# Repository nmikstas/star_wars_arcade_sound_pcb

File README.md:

# star_wars_arcade_sound_pcb
Reproduction of the Star Wars arcade sound PCB. The PCB is complete but not yet verified.

# Folder Structure
* BOM - Bill of materials for the sound PCB
* Gerbers - The gerber files for the sound PCB
* images - The images used for the sound PCB
* pcb - The Kicad design files for the sound PCB

# PCB Specifications
* Layers: 2
* Dimensions: 293mm X 227mm
* Different PCB Design: 1
* PCB Thickness: 1.6mm
* Surface Finish: HASL
* Castellated Holes: No
* Copper Weight: 1oz.

# The Complete Star Wars Arcade PCB Repository Collection
* Main PCB: https://github.com/nmikstas/star_wars_arcade_main_pcb
* AVG PCB: https://github.com/nmikstas/star_wars_arcade_avg_pcb
* Sound PCB: https://github.com/nmikstas/star_wars_arcade_sound_pcb
* EMI PCB: https://github.com/nmikstas/star_wars_arcade_emi_pcb
* Interconnect PCB: 
* AVG Chip: https://github.com/nmikstas/atari-avg-replacements
* Varistor Replacement: https://github.com/nmikstas/atari_voltage_dependent_resistor
* Mathbox ROM Replacement:
* State Machine Adapter PCB:

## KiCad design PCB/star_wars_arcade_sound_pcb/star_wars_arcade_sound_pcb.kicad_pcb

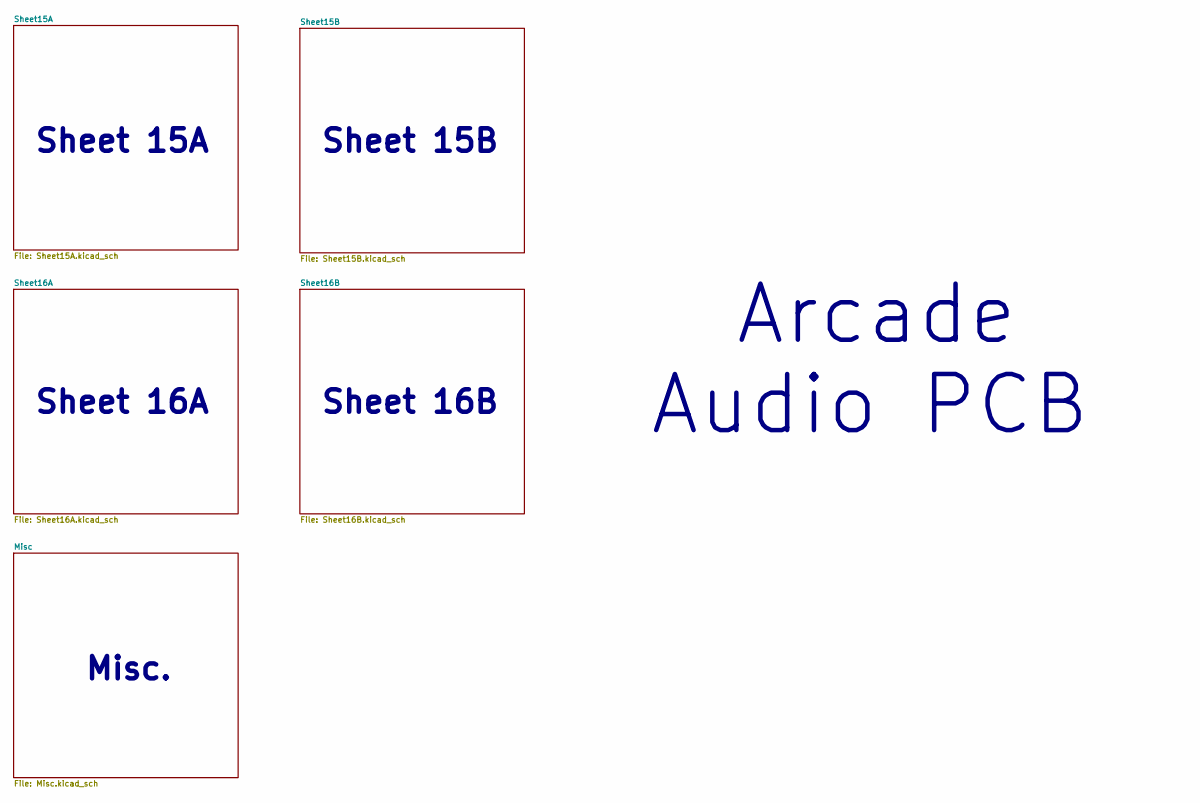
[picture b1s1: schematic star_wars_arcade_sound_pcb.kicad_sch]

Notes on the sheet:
Sheet 15A
Sheet 16A
Sheet 15B
Arcade Audio PCB
Sheet 16B
Misc.

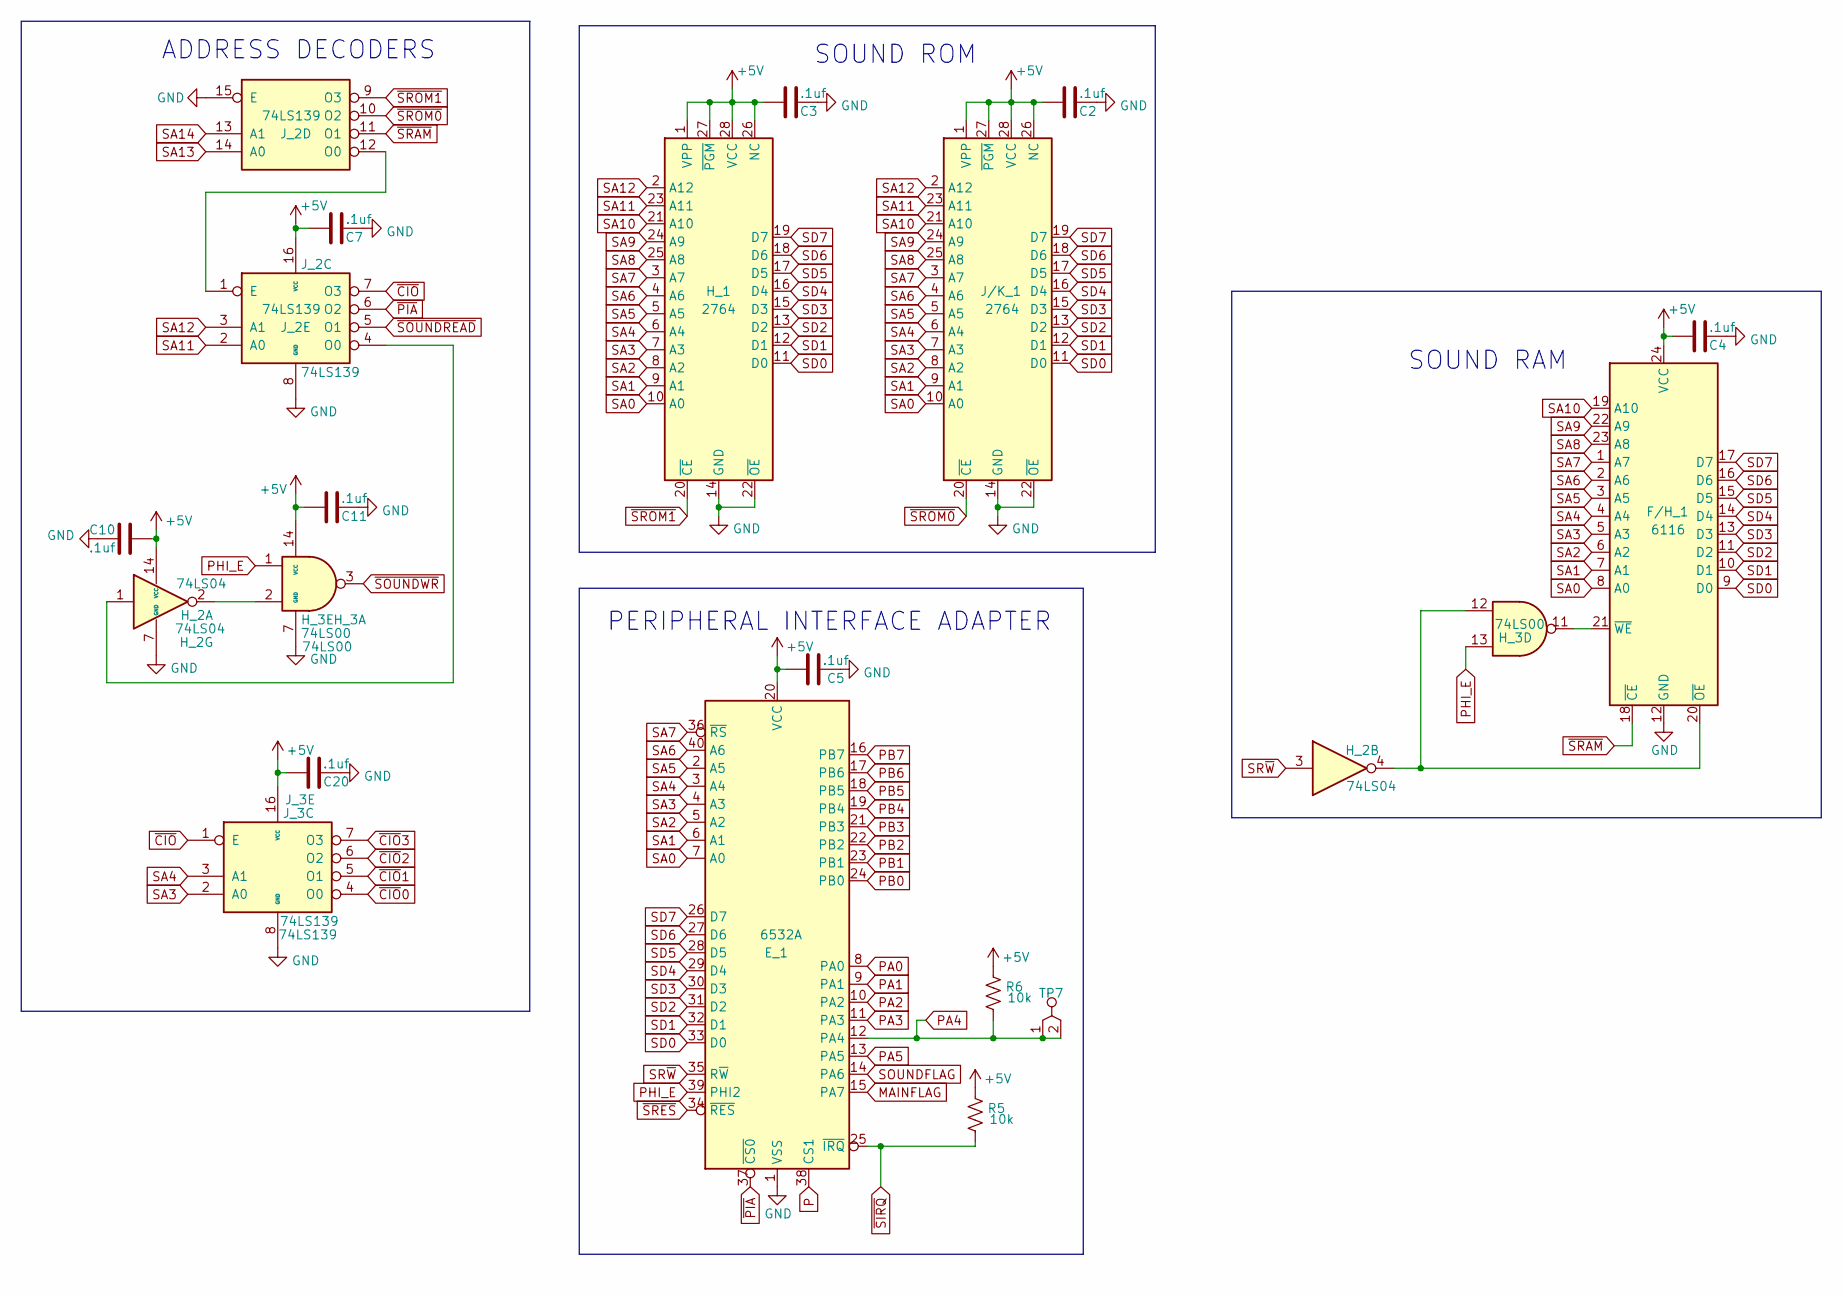
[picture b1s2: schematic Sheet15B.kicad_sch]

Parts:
C2, C3, C4, C5, C7, C10, C11, C20: .1uf; GenericComp
E_1: 6532A; DDIP40
F/H_1: 6116; DDIP24
H_1: 2764; DIP28
H_2: 74LS04; DIP14
H_3: 74LS00; DIP14
J/K_1: 2764; DIP28
J_2, J_3: 74LS139; DIP16
R5, R6: 10k; GenericComp
TP7: tp_2_pin; TEST_POINT

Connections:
+5V: C2.1, C3.1, C4.1, C5.1, C7.1, C10.1, C11.1, C20.1, E_1.20 (VCC), F/H_1.24 (VCC), H_1.1 (VPP), H_1.26 (NC), H_1.27 (~PGM), H_1.28 (VCC), H_2.14 (VCC), H_3.14 (VCC), J/K_1.1 (VPP), J/K_1.26 (NC), J/K_1.27 (~PGM), J/K_1.28 (VCC), J_2.16 (VCC), J_3.16 (VCC), R5.1, R6.1; also elsewhere on the board
GND: C2.2, C3.2, C4.2, C5.2, C7.2, C10.2, C11.2, C20.2, E_1.1 (VSS), F/H_1.12 (GND), H_1.14 (GND), H_1.22 (~OE), H_2.7 (GND), H_3.7 (GND), J/K_1.14 (GND), J/K_1.22 (~OE), J_2.8 (GND), J_2.15 (E), J_3.8 (GND); also elsewhere on the board
MAINFLAG: E_1.15 (PA7); also elsewhere on the board
unnamed: F/H_1.20 (~OE), H_2.4, H_3.12
unnamed: F/H_1.21 (~WE), H_3.11
unnamed: H_2.1, J_2.4 (O0)
unnamed: H_2.2, H_3.2
unnamed: J_2.1 (E), J_2.12 (O0)
P: E_1.38 (CS1); also elsewhere on the board
PA0: E_1.8 (PA0); also elsewhere on the board
PA1: E_1.9 (PA1); also elsewhere on the board
PA2: E_1.10 (PA2); also elsewhere on the board
PA3: E_1.11 (PA3); also elsewhere on the board
PA4: E_1.12 (PA4), R6.2, TP7.1, TP7.2
PA5: E_1.13 (PA5); also elsewhere on the board
PB0: E_1.24 (PB0); also elsewhere on the board
PB1: E_1.23 (PB1); also elsewhere on the board
PB2: E_1.22 (PB2); also elsewhere on the board
PB3: E_1.21 (PB3); also elsewhere on the board
PB4: E_1.19 (PB4); also elsewhere on the board
PB5: E_1.18 (PB5); also elsewhere on the board
PB6: E_1.17 (PB6); also elsewhere on the board
PB7: E_1.16 (PB7); also elsewhere on the board
PHI_E: E_1.39 (PHI2), H_3.1, H_3.13; also elsewhere on the board
SA0: E_1.7 (A0), F/H_1.8 (A0), H_1.10 (A0), J/K_1.10 (A0); also elsewhere on the board
SA1: E_1.6 (A1), F/H_1.7 (A1), H_1.9 (A1), J/K_1.9 (A1); also elsewhere on the board
SA2: E_1.5 (A2), F/H_1.6 (A2), H_1.8 (A2), J/K_1.8 (A2); also elsewhere on the board
SA3: E_1.4 (A3), F/H_1.5 (A3), H_1.7 (A3), J/K_1.7 (A3), J_3.2 (A0); also elsewhere on the board
SA4: E_1.3 (A4), F/H_1.4 (A4), H_1.6 (A4), J/K_1.6 (A4), J_3.3 (A1); also elsewhere on the board
SA5: E_1.2 (A5), F/H_1.3 (A5), H_1.5 (A5), J/K_1.5 (A5); also elsewhere on the board
SA6: E_1.40 (A6), F/H_1.2 (A6), H_1.4 (A6), J/K_1.4 (A6); also elsewhere on the board
SA7: E_1.36 (~RS), F/H_1.1 (A7), H_1.3 (A7), J/K_1.3 (A7); also elsewhere on the board
SA8: F/H_1.23 (A8), H_1.25 (A8), J/K_1.25 (A8); also elsewhere on the board
SA9: F/H_1.22 (A9), H_1.24 (A9), J/K_1.24 (A9); also elsewhere on the board
SA10: F/H_1.19 (A10), H_1.21 (A10), J/K_1.21 (A10); also elsewhere on the board
SA11: H_1.23 (A11), J/K_1.23 (A11), J_2.2 (A0); also elsewhere on the board
SA12: H_1.2 (A12), J/K_1.2 (A12), J_2.3 (A1); also elsewhere on the board
SA13: J_2.14 (A0); also elsewhere on the board
SA14: J_2.13 (A1); also elsewhere on the board
SD0: E_1.33 (D0), F/H_1.9 (D0), H_1.11 (D0), J/K_1.11 (D0); also elsewhere on the board
SD1: E_1.32 (D1), F/H_1.10 (D1), H_1.12 (D1), J/K_1.12 (D1); also elsewhere on the board
SD2: E_1.31 (D2), F/H_1.11 (D2), H_1.13 (D2), J/K_1.13 (D2); also elsewhere on the board
SD3: E_1.30 (D3), F/H_1.13 (D3), H_1.15 (D3), J/K_1.15 (D3); also elsewhere on the board
SD4: E_1.29 (D4), F/H_1.14 (D4), H_1.16 (D4), J/K_1.16 (D4); also elsewhere on the board
SD5: E_1.28 (D5), F/H_1.15 (D5), H_1.17 (D5), J/K_1.17 (D5); also elsewhere on the board
SD6: E_1.27 (D6), F/H_1.16 (D6), H_1.18 (D6), J/K_1.18 (D6); also elsewhere on the board
SD7: E_1.26 (D7), F/H_1.17 (D7), H_1.19 (D7), J/K_1.19 (D7); also elsewhere on the board
SOUNDFLAG: E_1.14 (PA6); also elsewhere on the board
SR~W: E_1.35 (R~W), H_2.3; also elsewhere on the board
~CIO: J_2.7 (O3), J_3.1 (E)
~CIO0: J_3.4 (O0); also elsewhere on the board
~CIO1: J_3.5 (O1); also elsewhere on the board
~CIO2: J_3.6 (O2); also elsewhere on the board
~CIO3: J_3.7 (O3); also elsewhere on the board
~PIA: E_1.37 (~CS0), J_2.6 (O2)
~SIRQ: E_1.25 (~IRQ), R5.2; also elsewhere on the board
~SOUNDREAD: J_2.5 (O1); also elsewhere on the board
~SOUNDWR: H_3.3; also elsewhere on the board
~SRAM: F/H_1.18 (~CE), J_2.11 (O1)
~SRES: E_1.34 (~RES); also elsewhere on the board
~SROM0: J/K_1.20 (~CE), J_2.10 (O2)
~SROM1: H_1.20 (~CE), J_2.9 (O3)

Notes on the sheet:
PERIPHERAL INTERFACE ADAPTER
ADDRESS DECODERS
SOUND RAM
SOUND ROM

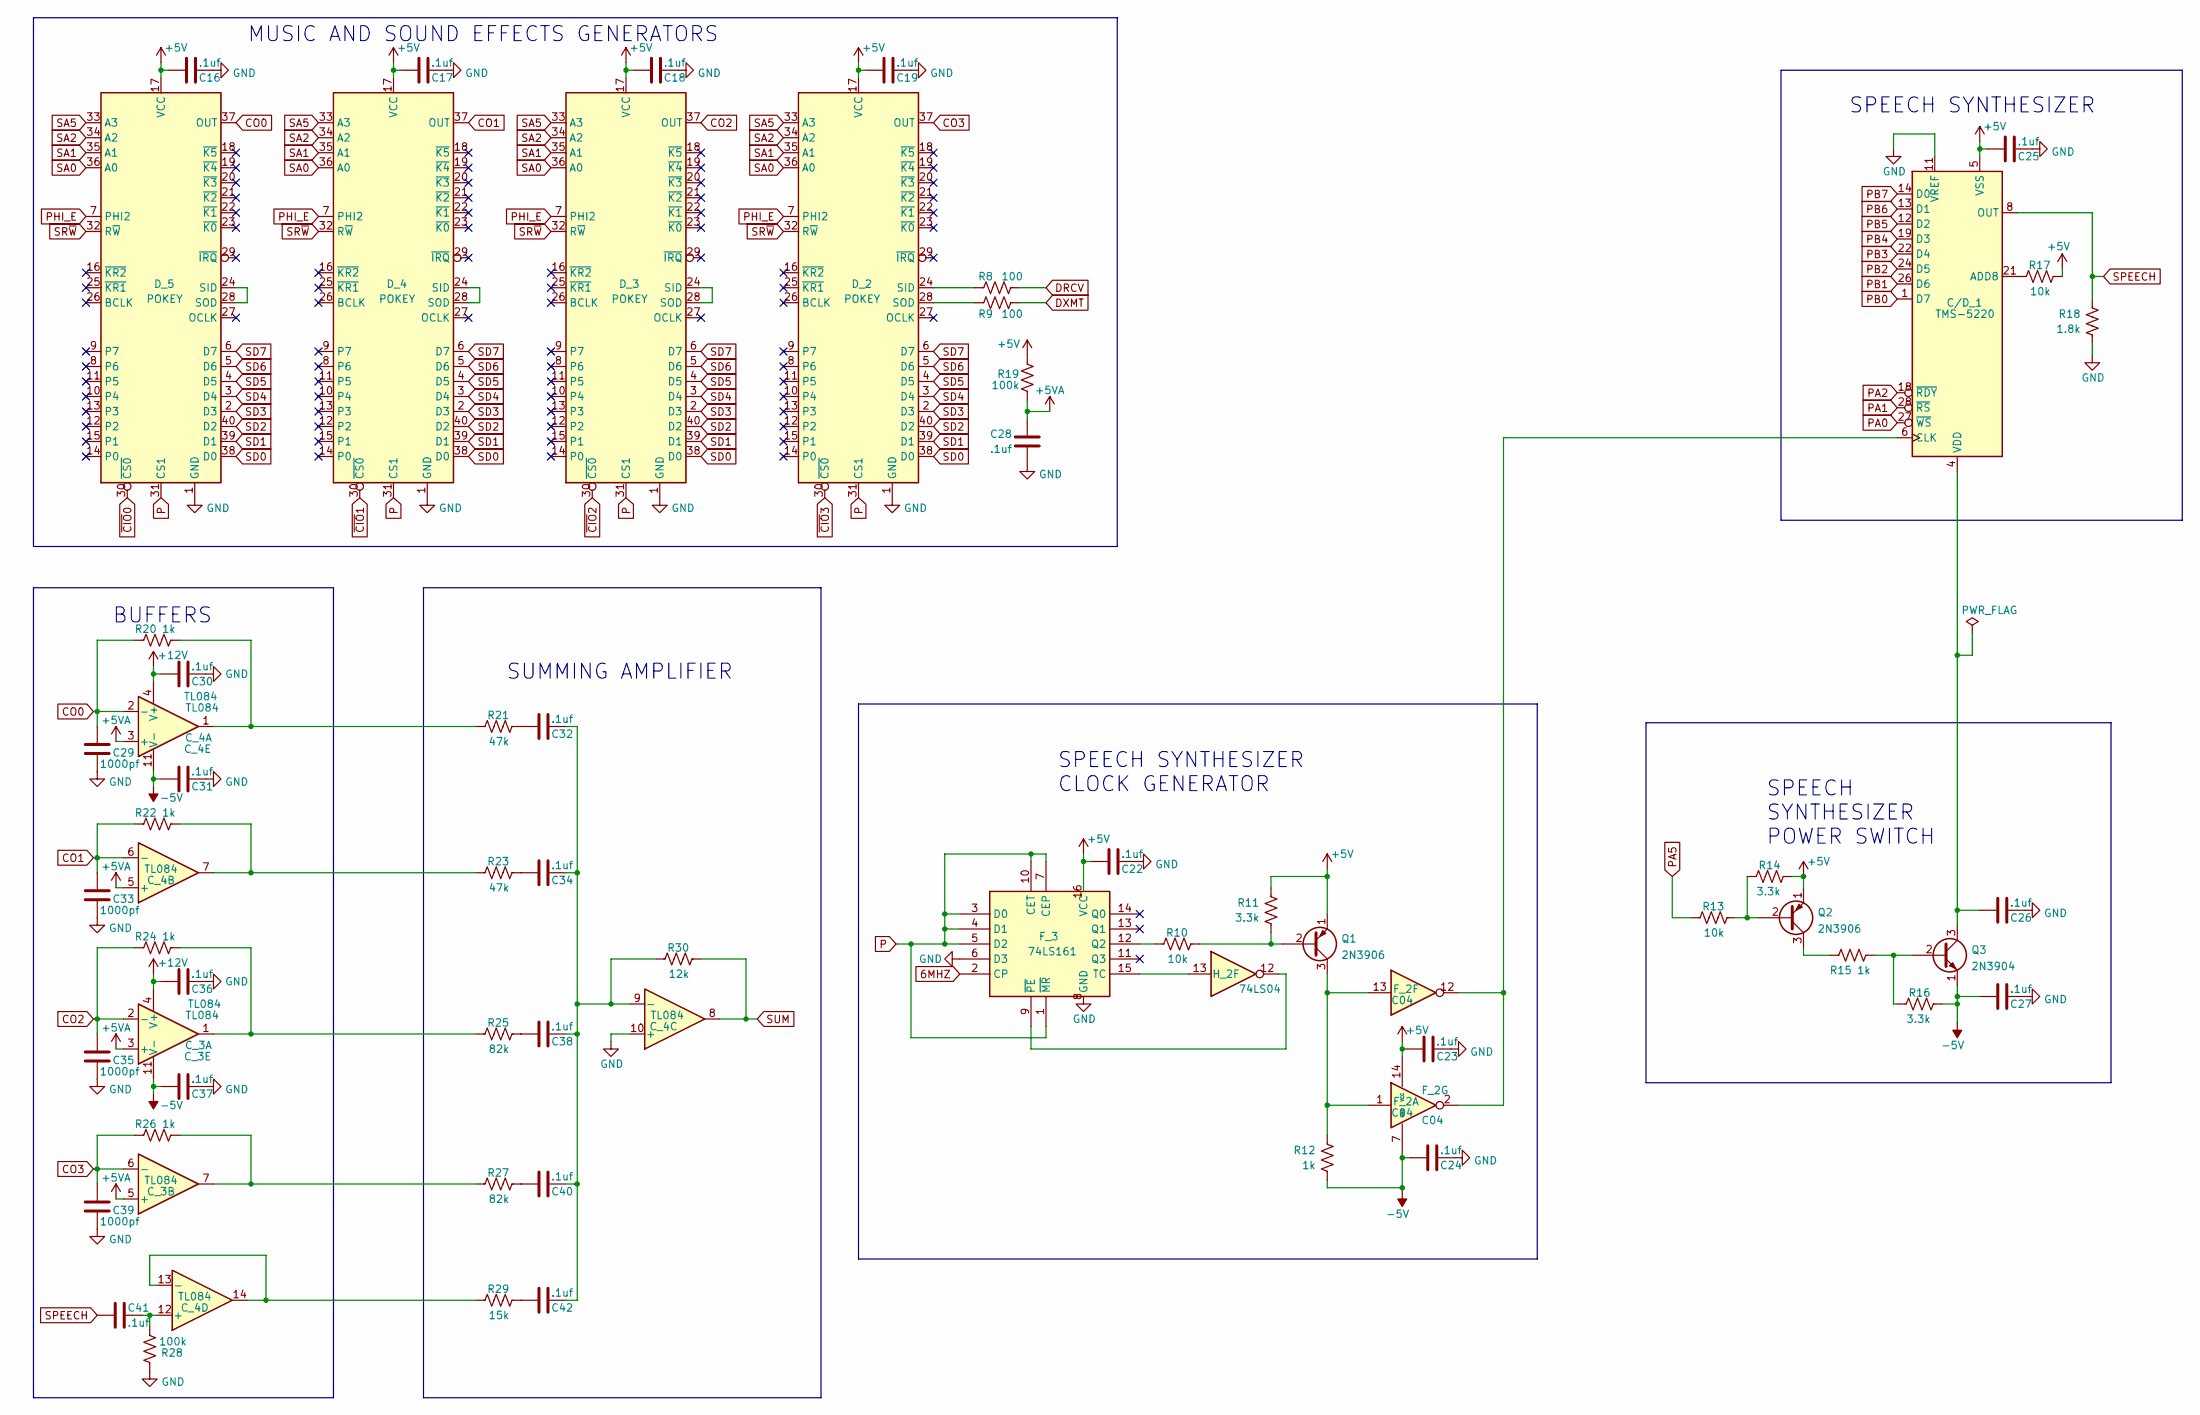
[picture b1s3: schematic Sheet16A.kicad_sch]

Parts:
C16, C17, C18, C19, C22, C23, C24, C25, C26, C27, C28, C30, C31, C32, C34, C36, C37, C38, C40, C41, C42: .1uf; GenericComp
C29, C33, C35, C39: 1000pf; GenericComp
C/D_1: TMS-5220; DIP28
C_3, C_4: TL084; DIP14
D_2, D_3, D_4, D_5: POKEY; DDIP40
F_2: C04; DIP14
F_3: 74LS161; DIP16
H_2: 74LS04; DIP14
Q1, Q2: 2N3906; GenericTrans
Q3: 2N3904; GenericTrans
R8, R9: 100; GenericComp
R10, R13, R17: 10k; GenericComp
R11, R14, R16: 3.3k; GenericComp
R12, R15, R20, R22, R24, R26: 1k; GenericComp
R18: 1.8k; GenericComp
R19, R28: 100k; GenericComp
R21, R23: 47k; GenericComp
R25, R27: 82k; GenericComp
R29: 15k; GenericComp
R30: 12k; GenericComp

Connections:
6MHZ: F_3.2 (CP); also elsewhere on the board
+5V: C16.1, C17.1, C18.1, C19.1, C22.1, C23.1, C25.1, C/D_1.5 (VSS), D_2.17 (VCC), D_3.17 (VCC), D_4.17 (VCC), D_5.17 (VCC), F_2.14 (VCC), F_3.16 (VCC), Q1.1 (E), Q2.1 (E), R11.2, R14.2, R17.2, R19.2; also elsewhere on the board
+5VA: C28.2, C_3.3 (+), C_3.5 (+), C_4.3 (+), C_4.5 (+), R19.1
+12V: C30.1, C36.1, C_3.4 (V+), C_4.4 (V+); also elsewhere on the board
-5V: C24.1, C27.1, C31.1, C37.1, C_3.11 (V-), C_4.11 (V-), F_2.7 (GND), Q3.1 (E), R12.1, R16.2; also elsewhere on the board
CO0: C29.2, C_4.2 (-), D_5.37 (OUT), R20.1
CO1: C33.2, C_4.6 (-), D_4.37 (OUT), R22.1
CO2: C35.2, C_3.2 (-), D_3.37 (OUT), R24.1
CO3: C39.2, C_3.6 (-), D_2.37 (OUT), R26.1
DRCV: R8.2; also elsewhere on the board
DXMT: R9.2; also elsewhere on the board
GND: C16.2, C17.2, C18.2, C19.2, C22.2, C23.2, C24.2, C25.2, C26.2, C27.2, C28.1, C29.1, C30.2, C31.2, C33.1, C35.1, C36.2, C37.2, C39.1, C/D_1.11 (VREF), C_4.10 (+), D_2.1 (GND), D_3.1 (GND), D_4.1 (GND), D_5.1 (GND), F_3.6 (D3), F_3.8 (GND), R18.1, R28.1; also elsewhere on the board
unnamed: C32.1, R21.2
unnamed: C32.2, C34.2, C38.2, C40.2, C42.2, C_4.9 (-), R30.1
unnamed: C34.1, R23.2
unnamed: C38.1, R25.2
unnamed: C40.1, R27.2
unnamed: C41.1, C_4.12 (+), R28.2
unnamed: C42.1, R29.2
unnamed: C26.1, C/D_1.4 (VDD), Q3.3 (C)
unnamed: C/D_1.6 (CLK), F_2.2, F_2.12
unnamed: C/D_1.21 (ADD8), R17.1
unnamed: C_3.1, R24.2, R25.1
unnamed: C_3.7, R26.2, R27.1
unnamed: C_4.1, R20.2, R21.1
unnamed: C_4.7, R22.2, R23.1
unnamed: C_4.13 (-), C_4.14, R29.1
unnamed: D_2.24 (SID), R8.1
unnamed: D_2.28 (SOD), R9.1
unnamed: D_3.24 (SID), D_3.28 (SOD)
unnamed: D_4.24 (SID), D_4.28 (SOD)
unnamed: D_5.24 (SID), D_5.28 (SOD)
unnamed: F_2.1, F_2.13, Q1.3 (C), R12.2
unnamed: F_3.9 (~PE), H_2.12
unnamed: F_3.12 (Q2), R10.1
unnamed: F_3.15 (TC), H_2.13
unnamed: Q1.2 (B), R10.2, R11.1
unnamed: Q2.2 (B), R13.2, R14.1
unnamed: Q2.3 (C), R15.1
unnamed: Q3.2 (B), R15.2, R16.1
P: D_2.31 (CS1), D_3.31 (CS1), D_4.31 (CS1), D_5.31 (CS1), F_3.1 (~MR), F_3.3 (D0), F_3.4 (D1), F_3.5 (D2), F_3.7 (CEP), F_3.10 (CET); also elsewhere on the board
PA0: C/D_1.27 (~WS); also elsewhere on the board
PA1: C/D_1.28 (~RS); also elsewhere on the board
PA2: C/D_1.18 (~RDY); also elsewhere on the board
PA5: R13.1; also elsewhere on the board
PB0: C/D_1.1 (D7); also elsewhere on the board
PB1: C/D_1.26 (D6); also elsewhere on the board
PB2: C/D_1.24 (D5); also elsewhere on the board
PB3: C/D_1.22 (D4); also elsewhere on the board
PB4: C/D_1.19 (D3); also elsewhere on the board
PB5: C/D_1.12 (D2); also elsewhere on the board
PB6: C/D_1.13 (D1); also elsewhere on the board
PB7: C/D_1.14 (D0); also elsewhere on the board
PHI_E: D_2.7 (PHI2), D_3.7 (PHI2), D_4.7 (PHI2), D_5.7 (PHI2); also elsewhere on the board
SA0: D_2.36 (A0), D_3.36 (A0), D_4.36 (A0), D_5.36 (A0); also elsewhere on the board
SA1: D_2.35 (A1), D_3.35 (A1), D_4.35 (A1), D_5.35 (A1); also elsewhere on the board
SA2: D_2.34 (A2), D_3.34 (A2), D_4.34 (A2), D_5.34 (A2); also elsewhere on the board
SA5: D_2.33 (A3), D_3.33 (A3), D_4.33 (A3), D_5.33 (A3); also elsewhere on the board
SD0: D_2.38 (D0), D_3.38 (D0), D_4.38 (D0), D_5.38 (D0); also elsewhere on the board
SD1: D_2.39 (D1), D_3.39 (D1), D_4.39 (D1), D_5.39 (D1); also elsewhere on the board
SD2: D_2.40 (D2), D_3.40 (D2), D_4.40 (D2), D_5.40 (D2); also elsewhere on the board
SD3: D_2.2 (D3), D_3.2 (D3), D_4.2 (D3), D_5.2 (D3); also elsewhere on the board
SD4: D_2.3 (D4), D_3.3 (D4), D_4.3 (D4), D_5.3 (D4); also elsewhere on the board
SD5: D_2.4 (D5), D_3.4 (D5), D_4.4 (D5), D_5.4 (D5); also elsewhere on the board
SD6: D_2.5 (D6), D_3.5 (D6), D_4.5 (D6), D_5.5 (D6); also elsewhere on the board
SD7: D_2.6 (D7), D_3.6 (D7), D_4.6 (D7), D_5.6 (D7); also elsewhere on the board
SPEECH: C41.2, C/D_1.8 (OUT), R18.2
SR~W: D_2.32 (R~W), D_3.32 (R~W), D_4.32 (R~W), D_5.32 (R~W); also elsewhere on the board
SUM: C_4.8, R30.2; also elsewhere on the board
~CIO0: D_5.30 (~CS0); also elsewhere on the board
~CIO1: D_4.30 (~CS0); also elsewhere on the board
~CIO2: D_3.30 (~CS0); also elsewhere on the board
~CIO3: D_2.30 (~CS0); also elsewhere on the board

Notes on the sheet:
SPEECH SYNTHESIZER CLOCK GENERATOR
BUFFERS
SPEECH SYNTHESIZER POWER SWITCH
MUSIC AND SOUND EFFECTS GENERATORS
SPEECH SYNTHESIZER
SUMMING AMPLIFIER

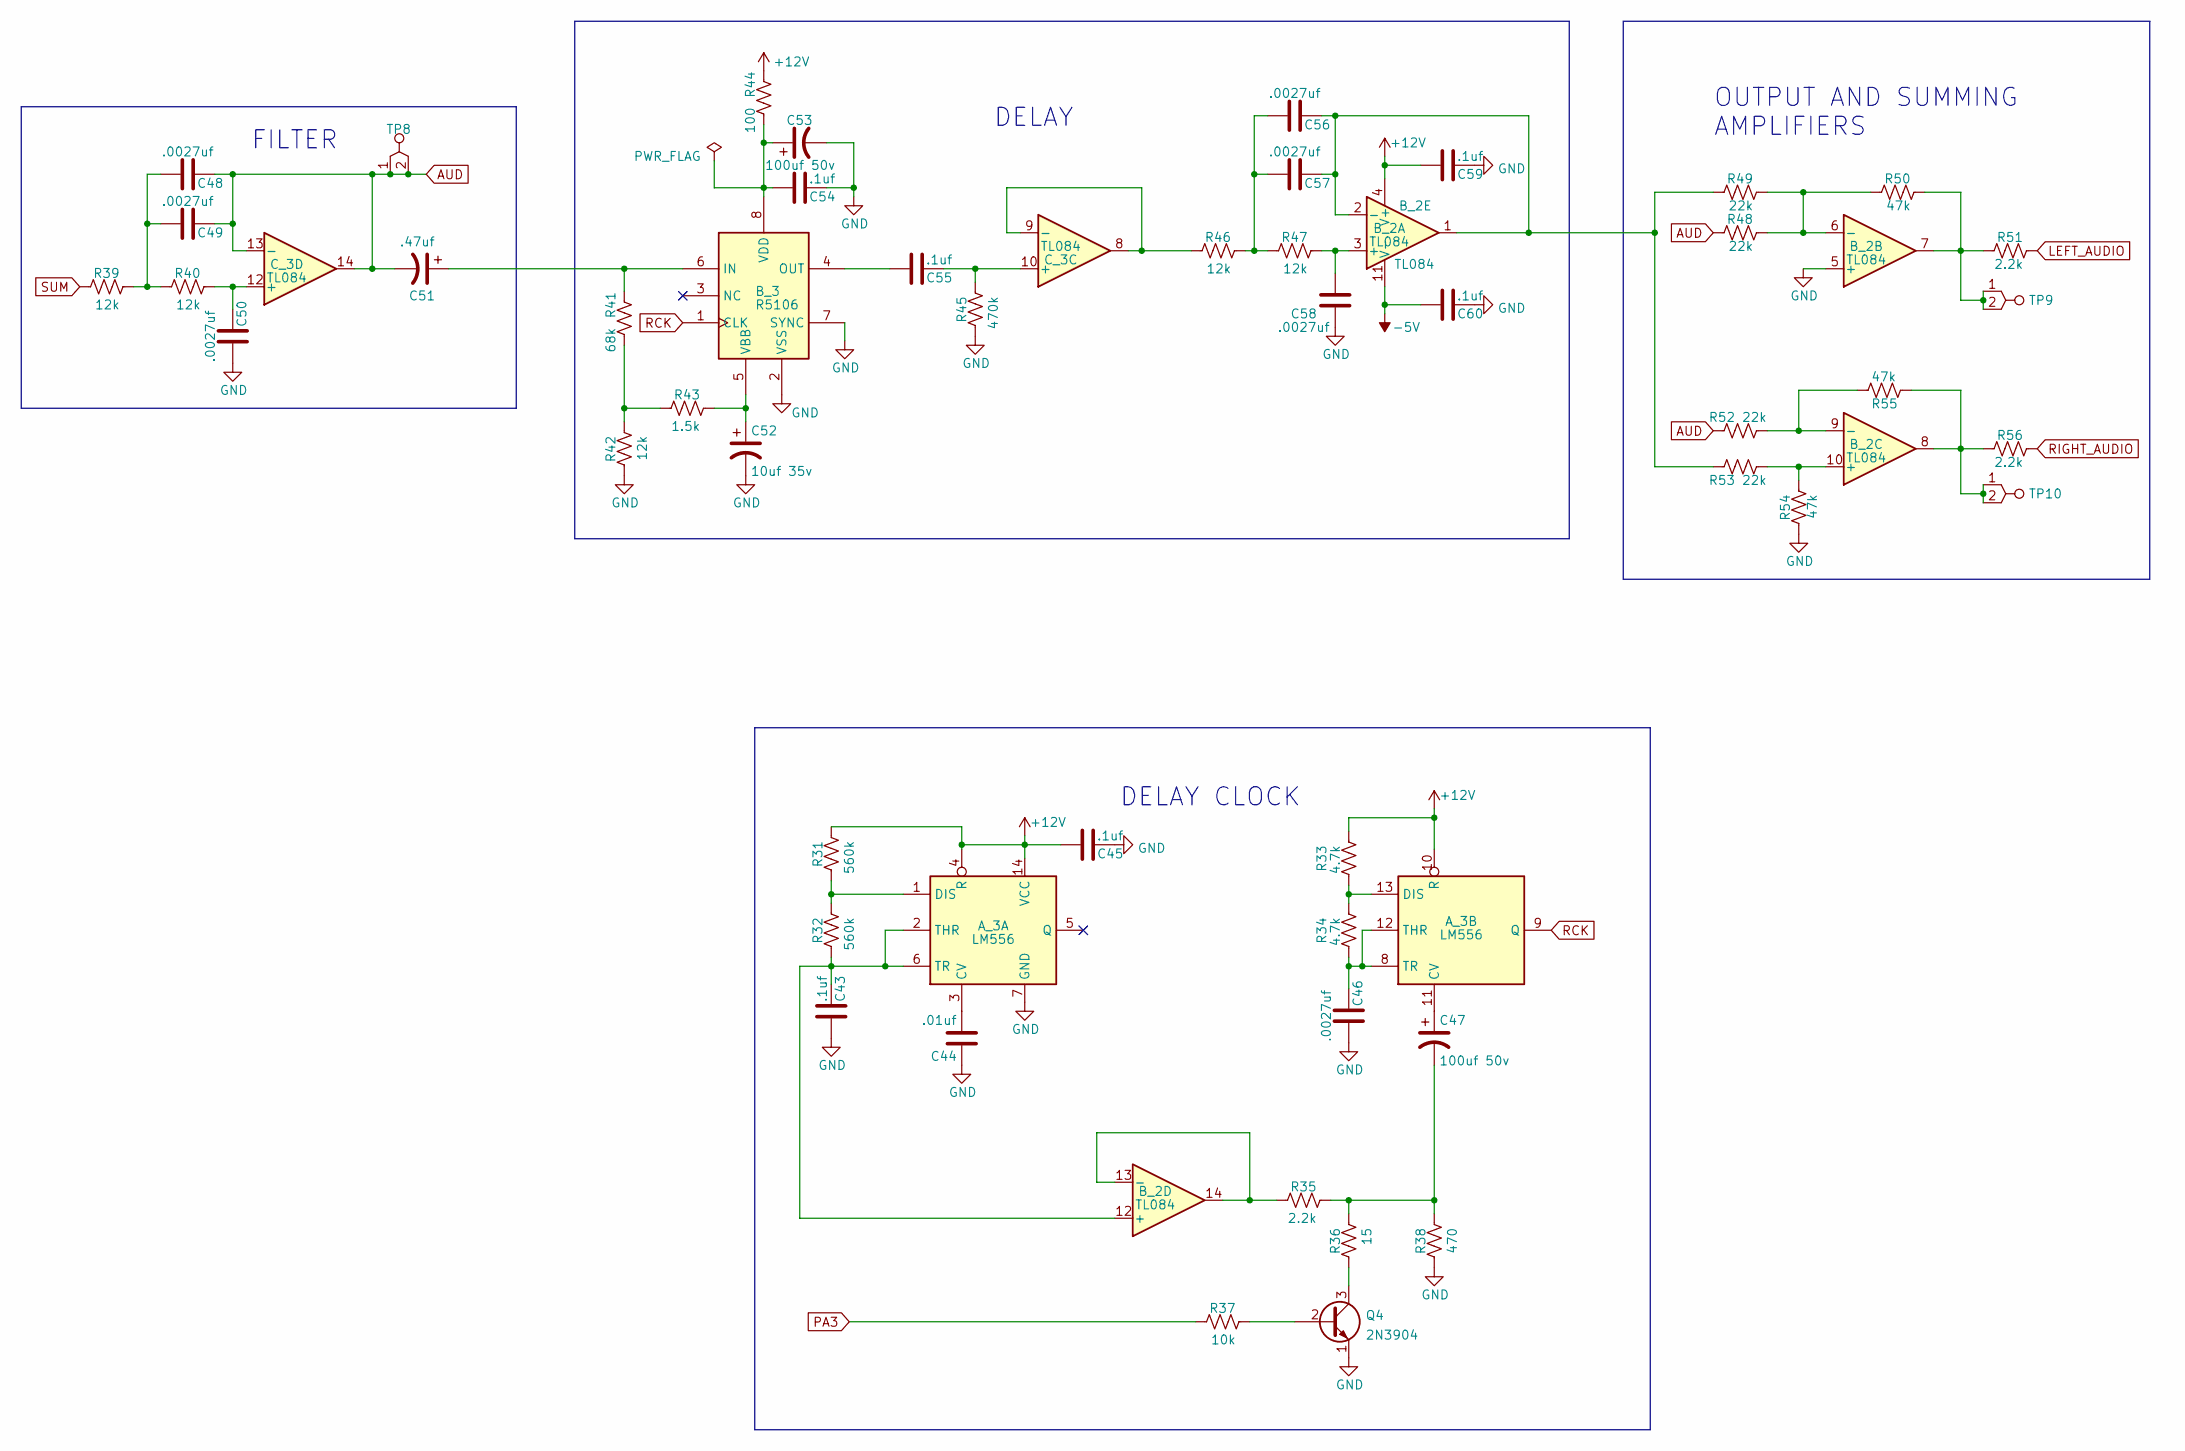
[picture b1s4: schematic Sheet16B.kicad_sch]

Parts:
A_3: LM556; DIP14
B_2: TL084; DIP14
B_3: R5106; DIP8
C43, C45, C54, C55, C59, C60: .1uf; GenericComp
C44: .01uf; GenericComp
C46, C48, C49, C50, C56, C57, C58: .0027uf; GenericComp
C47, C53: 100uf 50v; LargeCap1
C51: .47uf; MedCap1
C52: 10uf 35v; MedCap1
C_3: TL084; DIP14
Q4: 2N3904; GenericTrans
R31, R32: 560k; GenericComp
R33, R34: 4.7k; GenericComp
R35, R51, R56: 2.2k; GenericComp
R36: 15; GenericComp
R37: 10k; GenericComp
R38: 470; GenericComp
R39, R40, R42, R46, R47: 12k; GenericComp
R41: 68k; GenericComp
R43: 1.5k; GenericComp
R44: 100; GenericComp
R45: 470k; GenericComp
R48, R49, R52, R53: 22k; GenericComp
R50, R54, R55: 47k; GenericComp
TP8, TP9, TP10: tp_2_pin; TEST_POINT

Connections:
+12V: A_3.4 (R), A_3.10 (R), A_3.14 (VCC), B_2.4 (V+), C45.1, C59.1, R31.2, R33.2, R44.2; also elsewhere on the board
-5V: B_2.11 (V-), C60.1; also elsewhere on the board
AUD: C48.2, C49.2, C51.2, C_3.13 (-), C_3.14, R48.1, R52.1, TP8.1, TP8.2
GND: A_3.7 (GND), B_2.5 (+), B_3.2 (VSS), B_3.7 (SYNC), C43.1, C44.1, C45.2, C46.1, C50.1, C52.2, C53.2, C54.2, C58.1, C59.2, C60.2, Q4.1 (E), R38.1, R42.1, R45.1, R54.1; also elsewhere on the board
LEFT_AUDIO: R51.2; also elsewhere on the board
unnamed: A_3.1 (DIS), R31.1, R32.2
unnamed: A_3.2 (THR), A_3.6 (TR), B_2.12 (+), C43.2, R32.1
unnamed: A_3.3 (CV), C44.2
unnamed: A_3.11 (CV), C47.1
unnamed: A_3.8 (TR), A_3.12 (THR), C46.2, R34.1
unnamed: A_3.13 (DIS), R33.1, R34.2
unnamed: B_2.1, B_2.2 (-), C56.2, C57.2, R49.1, R53.1
unnamed: B_2.3 (+), C58.2, R47.2
unnamed: B_2.6 (-), R48.2, R49.2, R50.1
unnamed: B_2.7, R50.2, R51.1, TP9.1, TP9.2
unnamed: B_2.8, R55.1, R56.1, TP10.1, TP10.2
unnamed: B_2.9 (-), R52.2, R55.2
unnamed: B_2.10 (+), R53.2, R54.2
unnamed: B_2.13 (-), B_2.14, R35.1
unnamed: B_3.4 (OUT), C55.1
unnamed: B_3.5 (VBB), C52.1, R43.2
unnamed: B_3.6 (IN), C51.1, R41.2
unnamed: B_3.8 (VDD), C53.1, C54.1, R44.1
unnamed: C47.2, R35.2, R36.2, R38.2
unnamed: C48.1, C49.1, R39.2, R40.1
unnamed: C50.2, C_3.12 (+), R40.2
unnamed: C55.2, C_3.10 (+), R45.2
unnamed: C56.1, C57.1, R46.2, R47.1
unnamed: C_3.8, C_3.9 (-), R46.1
unnamed: Q4.2 (B), R37.2
unnamed: Q4.3 (C), R36.1
unnamed: R41.1, R42.2, R43.1
PA3: R37.1; also elsewhere on the board
RCK: A_3.9 (Q), B_3.1 (CLK)
RIGHT_AUDIO: R56.2; also elsewhere on the board
SUM: R39.1; also elsewhere on the board

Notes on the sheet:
OUTPUT AND SUMMING AMPLIFIERS
DELAY CLOCK
FILTER
DELAY

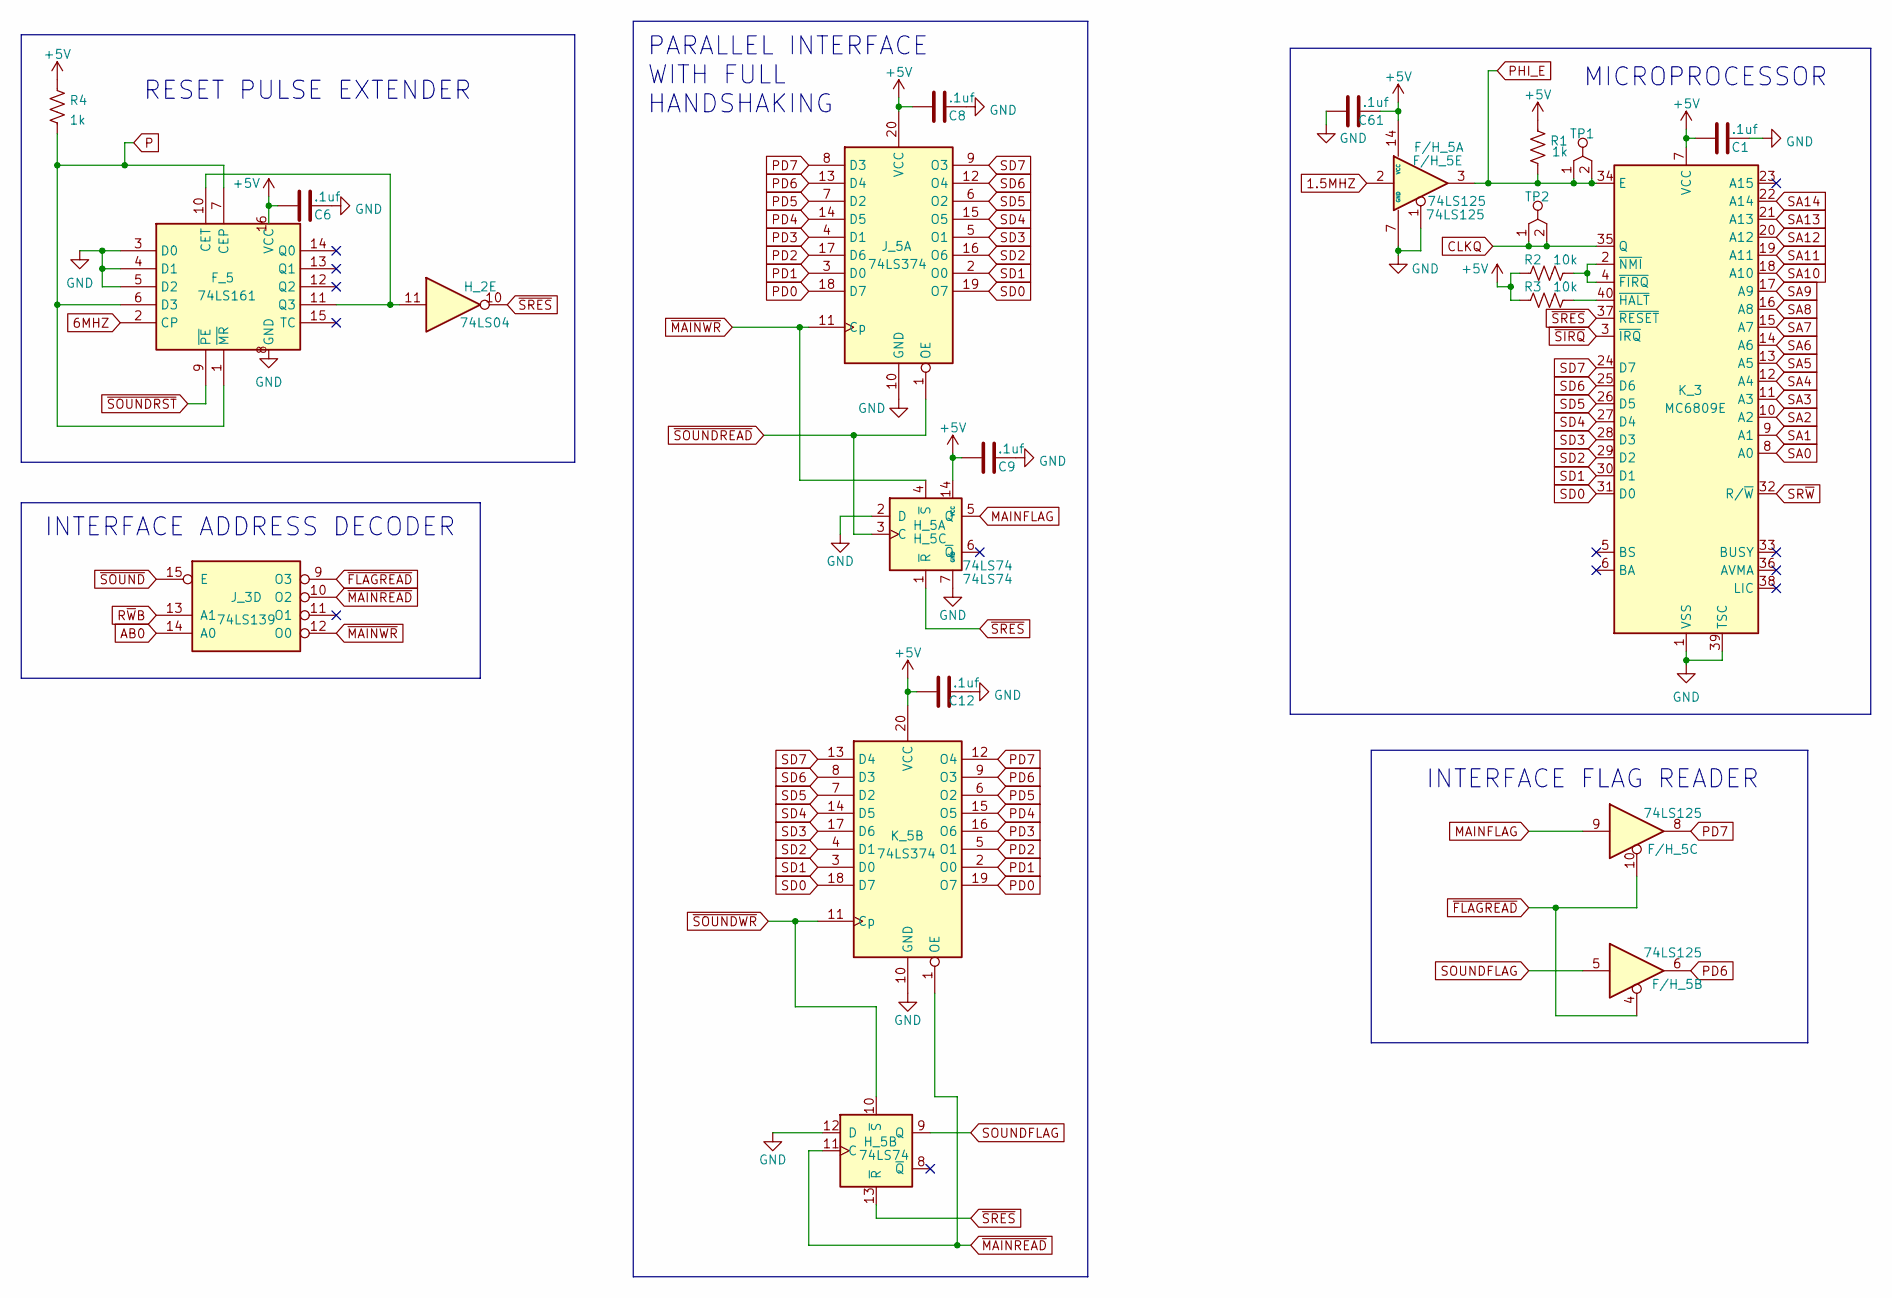
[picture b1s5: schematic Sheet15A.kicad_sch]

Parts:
C1, C6, C8, C9, C12, C61: .1uf; GenericComp
F/H_5: 74LS125; DIP14
F_5: 74LS161; DIP16
H_2: 74LS04; DIP14
H_5: 74LS74; DIP14
J_3: 74LS139; DIP16
J_5: 74LS374; DIP20
K_3: MC6809E; DDIP40
K_5: 74LS374; DIP20
R1, R4: 1k; GenericComp
R2, R3: 10k; GenericComp
TP1, TP2: tp_2_pin; TEST_POINT

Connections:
1.5MHZ: F/H_5.2; also elsewhere on the board
6MHZ: F_5.2 (CP); also elsewhere on the board
+5V: C1.1, C6.1, C8.1, C9.1, C12.1, C61.2, F/H_5.14 (VCC), F_5.16 (VCC), H_5.14 (VCC), J_5.20 (VCC), K_3.7 (VCC), K_5.20 (VCC), R1.1, R2.1, R3.1, R4.1; also elsewhere on the board
AB0: J_3.14 (A0); also elsewhere on the board
CLKQ: K_3.35 (Q), TP2.1, TP2.2; also elsewhere on the board
GND: C1.2, C6.2, C8.2, C9.2, C12.2, C61.1, F/H_5.1, F/H_5.7 (GND), F_5.3 (D0), F_5.4 (D1), F_5.5 (D2), F_5.8 (GND), H_5.2 (D), H_5.7 (GND), H_5.12 (D), J_5.10 (GND), K_3.1 (VSS), K_3.39 (TSC), K_5.10 (GND); also elsewhere on the board
MAINFLAG: F/H_5.9, H_5.5 (Q); also elsewhere on the board
unnamed: F_5.10 (CET), F_5.11 (Q3), H_2.11
unnamed: K_3.2 (~NMI), K_3.4 (~FIRQ), R2.2
unnamed: K_3.40 (~HALT), R3.2
P: F_5.1 (~MR), F_5.6 (D3), F_5.7 (CEP), R4.2; also elsewhere on the board
PD0: J_5.18 (D7), K_5.19 (O7); also elsewhere on the board
PD1: J_5.3 (D0), K_5.2 (O0); also elsewhere on the board
PD2: J_5.17 (D6), K_5.5 (O1); also elsewhere on the board
PD3: J_5.4 (D1), K_5.16 (O6); also elsewhere on the board
PD4: J_5.14 (D5), K_5.15 (O5); also elsewhere on the board
PD5: J_5.7 (D2), K_5.6 (O2); also elsewhere on the board
PD6: F/H_5.6, J_5.13 (D4), K_5.9 (O3); also elsewhere on the board
PD7: F/H_5.8, J_5.8 (D3), K_5.12 (O4); also elsewhere on the board
PHI_E: F/H_5.3, K_3.34 (E), R1.2, TP1.1, TP1.2; also elsewhere on the board
R~WB: J_3.13 (A1); also elsewhere on the board
SA0: K_3.8 (A0); also elsewhere on the board
SA1: K_3.9 (A1); also elsewhere on the board
SA2: K_3.10 (A2); also elsewhere on the board
SA3: K_3.11 (A3); also elsewhere on the board
SA4: K_3.12 (A4); also elsewhere on the board
SA5: K_3.13 (A5); also elsewhere on the board
SA6: K_3.14 (A6); also elsewhere on the board
SA7: K_3.15 (A7); also elsewhere on the board
SA8: K_3.16 (A8); also elsewhere on the board
SA9: K_3.17 (A9); also elsewhere on the board
SA10: K_3.18 (A10); also elsewhere on the board
SA11: K_3.19 (A11); also elsewhere on the board
SA12: K_3.20 (A12); also elsewhere on the board
SA13: K_3.21 (A13); also elsewhere on the board
SA14: K_3.22 (A14); also elsewhere on the board
SD0: J_5.19 (O7), K_3.31 (D0), K_5.18 (D7); also elsewhere on the board
SD1: J_5.2 (O0), K_3.30 (D1), K_5.3 (D0); also elsewhere on the board
SD2: J_5.16 (O6), K_3.29 (D2), K_5.4 (D1); also elsewhere on the board
SD3: J_5.5 (O1), K_3.28 (D3), K_5.17 (D6); also elsewhere on the board
SD4: J_5.15 (O5), K_3.27 (D4), K_5.14 (D5); also elsewhere on the board
SD5: J_5.6 (O2), K_3.26 (D5), K_5.7 (D2); also elsewhere on the board
SD6: J_5.12 (O4), K_3.25 (D6), K_5.8 (D3); also elsewhere on the board
SD7: J_5.9 (O3), K_3.24 (D7), K_5.13 (D4); also elsewhere on the board
SOUNDFLAG: F/H_5.5, H_5.9 (Q); also elsewhere on the board
SR~W: K_3.32 (R/~W); also elsewhere on the board
~FLAGREAD: F/H_5.4, F/H_5.10, J_3.9 (O3)
~MAINREAD: H_5.11 (C), J_3.10 (O2), K_5.1 (OE)
~MAINWR: H_5.4 (~S), J_3.12 (O0), J_5.11 (Cp)
~SIRQ: K_3.3 (~IRQ); also elsewhere on the board
~SOUNDREAD: H_5.3 (C), J_5.1 (OE); also elsewhere on the board
~SOUNDRST: F_5.9 (~PE); also elsewhere on the board
~SOUNDWR: H_5.10 (~S), K_5.11 (Cp); also elsewhere on the board
~SOUND: J_3.15 (E); also elsewhere on the board
~SRES: H_2.10, H_5.1 (~R), H_5.13 (~R), K_3.37 (~RESET); also elsewhere on the board

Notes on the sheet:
INTERFACE FLAG READER
PARALLEL INTERFACE WITH FULL HANDSHAKING
RESET PULSE EXTENDER
MICROPROCESSOR
INTERFACE ADDRESS DECODER
